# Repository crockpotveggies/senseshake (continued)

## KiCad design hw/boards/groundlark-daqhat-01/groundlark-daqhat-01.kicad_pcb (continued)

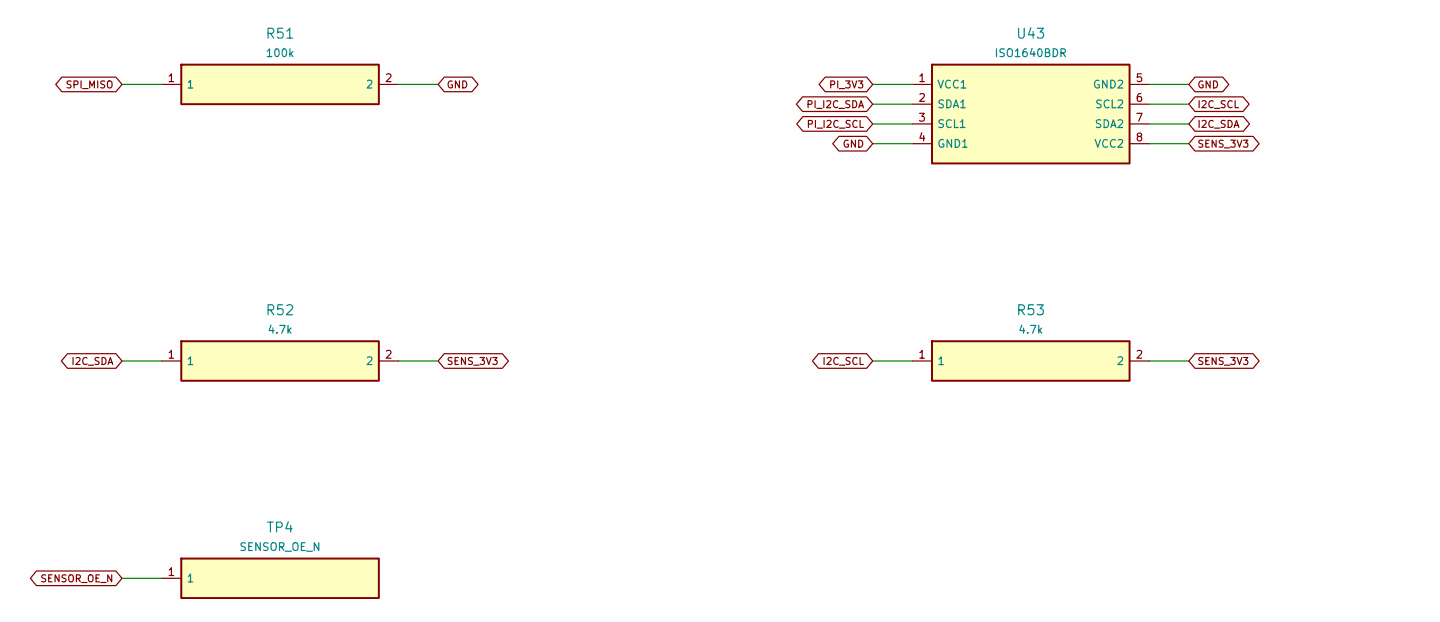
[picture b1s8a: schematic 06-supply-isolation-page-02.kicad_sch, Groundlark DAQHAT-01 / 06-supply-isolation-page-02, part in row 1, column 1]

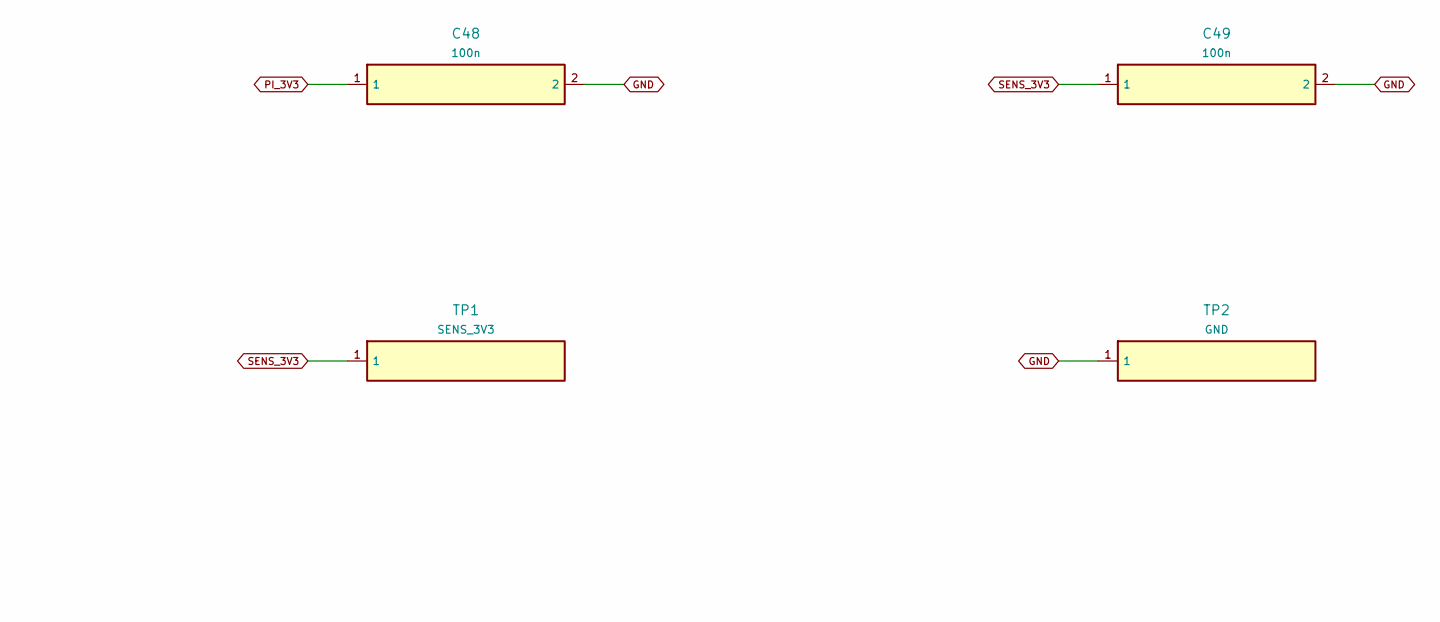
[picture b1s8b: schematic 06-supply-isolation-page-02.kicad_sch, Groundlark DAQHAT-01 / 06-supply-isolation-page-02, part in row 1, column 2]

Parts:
C48, C49: 100n; Capacitor_SMD__C_0603_1608Metric; MPN GRM188R71H104KA93D
R51: 100k; Resistor_SMD__R_0603_1608Metric; MPN RC0603FR-07100KL
R52, R53: 4.7k; Resistor_SMD__R_0603_1608Metric; MPN RC0603FR-074K7L
TP1: SENS_3V3; TestPoint__TestPoint_Pad_D1.5mm; MPN SENS_3V3
TP2: GND; TestPoint__TestPoint_Pad_D1.5mm; MPN GND
TP4: SENSOR_OE_N; TestPoint__TestPoint_Pad_D1.5mm; MPN SENSOR_OE_N
U43: ISO1640BDR; Package_SO__SOIC-8_3.9x4.9mm_P1.27mm; MPN ISO1640BDR

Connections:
GND: C48.2, C49.2, R51.2, TP2.1, U43.4 (GND1), U43.5 (GND2); also elsewhere on the board
I2C_SCL: R53.1, U43.6 (SCL2); also elsewhere on the board
I2C_SDA: R52.1, U43.7 (SDA2); also elsewhere on the board
PI_3V3: C48.1, U43.1 (VCC1); also elsewhere on the board
PI_I2C_SCL: U43.3 (SCL1); also elsewhere on the board
PI_I2C_SDA: U43.2 (SDA1); also elsewhere on the board
SENSOR_OE_N: TP4.1; also elsewhere on the board
SENS_3V3: C49.1, R52.2, R53.2, TP1.1, U43.8 (VCC2); also elsewhere on the board
SPI_MISO: R51.1; also elsewhere on the board

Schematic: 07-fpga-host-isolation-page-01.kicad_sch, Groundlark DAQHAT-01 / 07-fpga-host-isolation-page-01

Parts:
C75, C76, C77: 100n; Capacitor_SMD__C_0603_1608Metric; MPN GRM188R71H104KA93D
Q1: 2N7002; Package_TO_SOT_SMD__SOT-23; MPN 2N7002
R61: 47; Resistor_SMD__R_0603_1608Metric; MPN RC0603FR-0747RL
R62, R66: 100k; Resistor_SMD__R_0603_1608Metric; MPN RC0603FR-07100KL
R63, R64: 10k; Resistor_SMD__R_0603_1608Metric; MPN RC0603FR-0710KL
R65: 1k; Resistor_SMD__R_0603_1608Metric; MPN RC0603FR-071KL
U51: TXU0202DCUR; Package_SO__VSSOP-8_2.3x2mm_P0.5mm; MPN TXU0202DCUR
U52: TLV803EA30DBZR; Package_TO_SOT_SMD__SOT-23; MPN TLV803EA30DBZR

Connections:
FPGA_3V3: C76.1, C77.1, R63.2, R64.2, U51.7 (VCCB), U52.3 (VDD); also elsewhere on the board
FPGA_IO_ENABLE: R62.1, U51.6 (OE); also elsewhere on the board
FPGA_RESET_GATE: Q1.1 (G), R65.2, R66.1
FPGA_RESET_GPIO: R65.1; also elsewhere on the board
FPGA_RESET_N: Q1.3 (D), R64.1, U52.2 (RESET_N); also elsewhere on the board
FPGA_UART_DRIVE: R61.1, U51.8 (B1Y_OUT)
FPGA_UART_RX: R61.2, R63.1; also elsewhere on the board
FPGA_UART_TX: U51.1 (B2_IN); also elsewhere on the board
GND: C75.2, C76.2, C77.2, Q1.2 (S), R62.2, R66.2, U51.2 (GND), U52.1 (GND); also elsewhere on the board
PI_3V3: C75.1, U51.3 (VCCA); also elsewhere on the board
PI_UART_RX: U51.4 (A2Y_OUT); also elsewhere on the board
PI_UART_TX: U51.5 (A1_IN); also elsewhere on the board

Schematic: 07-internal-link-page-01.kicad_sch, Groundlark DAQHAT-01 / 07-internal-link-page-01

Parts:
C100, C101, C102, C103, C104, C105: 100n; Capacitor_SMD__C_0603_1608Metric; MPN GRM188R71H104KA93D
U100, U101: TMUX1574PWR; Package_SO__TSSOP-16_4.4x5mm_P0.65mm; MPN TMUX1574PWR
U102: TCA9534PWR; Package_SO__TSSOP-16_4.4x5mm_P0.65mm; MPN TCA9534PWR
U103: SN74LVC1G10DCKR; Package_TO_SOT_SMD__SOT-363_SC-70-6; MPN SN74LVC1G10DCKR
U104, U105: TLV809EA30DBZR; Package_TO_SOT_SMD__SOT-23; MPN TLV809EA30DBZR

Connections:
FPGA_3V3: C100.1, C101.1, C103.1, C105.1, U100.16 (VDD), U101.16 (VDD), U103.5 (VCC), U105.3 (VDD); also elsewhere on the board
FPGA_LINK_CS_N: U101.2 (S1A); also elsewhere on the board
FPGA_LINK_DQ0: U100.5 (S2A); also elsewhere on the board
FPGA_LINK_DQ1: U100.11 (S3A); also elsewhere on the board
FPGA_LINK_DQ2: U100.14 (S4A); also elsewhere on the board
FPGA_LINK_DQ3: U101.5 (S2A); also elsewhere on the board
FPGA_LINK_SCLK: U100.2 (S1A); also elsewhere on the board
GND: C100.2, C101.2, C102.2, C103.2, C104.2, C105.2, U100.8 (GND), U101.8 (GND), U101.9 (D3), U101.10 (S3B), U101.11 (S3A), U101.12 (D4), U101.13 (S4B), U101.14 (S4A), U102.1 (A0), U102.2 (A1), U102.3 (A2), U102.6 (P2), U102.7 (P3), U102.8 (GND), U102.9 (P4), U102.10 (P5), U102.11 (P6), U102.12 (P7), U103.2 (GND), U104.1 (GND), U105.1 (GND); also elsewhere on the board
JTAG_TCK: U100.3 (S1B); also elsewhere on the board
JTAG_TDI: U100.6 (S2B); also elsewhere on the board
JTAG_TDO: U100.10 (S3B); also elsewhere on the board
JTAG_TMS: U100.13 (S4B); also elsewhere on the board
LINK_ARMED_REQUEST: U103.1 (A); also elsewhere on the board
LINK_CS_N: U101.4 (D1); also elsewhere on the board
LINK_DQ0: U100.7 (D2); also elsewhere on the board
LINK_DQ1: U100.9 (D3); also elsewhere on the board
LINK_DQ2: U100.12 (D4); also elsewhere on the board
LINK_DQ3: U101.7 (D2); also elsewhere on the board
LINK_FPGA_GOOD: U103.6 (C), U105.2 (RESET_N); also elsewhere on the board
LINK_JTAG_SEL: U100.1 (SEL), U101.1 (SEL), U102.4 (P0_MODE); also elsewhere on the board
LINK_OE_N: U100.15 (EN_N), U101.15 (EN_N), U103.4 (Y); also elsewhere on the board
LINK_PI_GOOD: U103.3 (B), U104.2 (RESET_N); also elsewhere on the board
LINK_REQUEST: U102.5 (P1_ENABLE); also elsewhere on the board
LINK_SCLK: U100.4 (D1); also elsewhere on the board
PI_3V3: C102.1, C104.1, U102.16 (VCC), U104.3 (VDD); also elsewhere on the board
PI_I2C_SCL: U102.14 (SCL); also elsewhere on the board
PI_I2C_SDA: U102.15 (SDA); also elsewhere on the board
u101-3: U101.3 (S1B)
u101-6: U101.6 (S2B)
u102-13: U102.13 (INT_N)

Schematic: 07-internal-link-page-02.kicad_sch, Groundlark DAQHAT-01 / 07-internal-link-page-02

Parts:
R100, R101, R102, R103, R104, R105: 22; Resistor_SMD__R_0603_1608Metric; MPN RC0603FR-0722RL
R106, R107, R108, R109, R110, R111: 10k; Resistor_SMD__R_0603_1608Metric; MPN RC0603FR-0710KL

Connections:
FPGA_3V3: R108.2, R111.2; also elsewhere on the board
FPGA_LINK_CS_N: R111.1; also elsewhere on the board
GND: R106.2, R107.2, R109.2, R110.2; also elsewhere on the board
LINK_CS_N: R104.2; also elsewhere on the board
LINK_DQ0: R101.2; also elsewhere on the board
LINK_DQ1: R102.2; also elsewhere on the board
LINK_DQ2: R103.2; also elsewhere on the board
LINK_DQ3: R105.2; also elsewhere on the board
LINK_FPGA_GOOD: R110.1; also elsewhere on the board
LINK_JTAG_SEL: R106.1; also elsewhere on the board
LINK_OE_N: R108.1; also elsewhere on the board
LINK_PI_GOOD: R109.1; also elsewhere on the board
LINK_REQUEST: R107.1; also elsewhere on the board
LINK_SCLK: R100.2; also elsewhere on the board
PI_LINK_CS_N: R104.1; also elsewhere on the board
PI_LINK_DQ0: R101.1; also elsewhere on the board
PI_LINK_DQ1: R102.1; also elsewhere on the board
PI_LINK_DQ2: R103.1; also elsewhere on the board
PI_LINK_DQ3: R105.1; also elsewhere on the board
PI_LINK_SCLK: R100.1; also elsewhere on the board

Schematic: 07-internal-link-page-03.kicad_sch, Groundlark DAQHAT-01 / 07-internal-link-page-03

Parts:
C106: 100n; Capacitor_SMD__C_0603_1608Metric; MPN GRM188R71H104KA93D
R112, R114, R116, R117: 100k; Resistor_SMD__R_0603_1608Metric; MPN RC0603FR-07100KL
R113, R115: 10k; Resistor_SMD__R_0603_1608Metric; MPN RC0603FR-0710KL
U106: SN74LVC1G08DCKR; Package_TO_SOT_SMD__SOT-353_SC-70-5; MPN SN74LVC1G08DCKR

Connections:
FPGA_3V3: C106.1, R113.2, R115.2, U106.5 (VCC); also elsewhere on the board
FPGA_IO_ENABLE: U106.2 (B); also elsewhere on the board
FPGA_LINK_DQ2: R116.1; also elsewhere on the board
FPGA_LINK_DQ3: R117.1; also elsewhere on the board
FPGA_LINK_SCLK: R112.1; also elsewhere on the board
GND: C106.2, R112.2, R114.2, R116.2, R117.2, U106.3 (GND); also elsewhere on the board
JTAG_TCK: R114.1; also elsewhere on the board
JTAG_TDI: R115.1; also elsewhere on the board
JTAG_TMS: R113.1; also elsewhere on the board
LINK_ARMED_REQUEST: U106.4 (Y); also elsewhere on the board
LINK_REQUEST: U106.1 (A); also elsewhere on the board

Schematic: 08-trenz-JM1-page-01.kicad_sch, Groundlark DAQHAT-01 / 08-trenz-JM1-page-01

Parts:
J80: LSHM-150-04.0-L-DV-A-S-K-TR; TZ_TZ100; MPN LSHM-150-04.0-L-DV-A-S-K-TR

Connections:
3: J80.3
5: J80.5
9: J80.9
11: J80.11
15: J80.15
17: J80.17
20: J80.20
21: J80.21
22: J80.22
23: J80.23
24: J80.24
26: J80.26
28: J80.28
32: J80.32
34: J80.34
35: J80.35
36: J80.36
37: J80.37
38: J80.38
39: J80.39
40: J80.40
41: J80.41
42: J80.42
44: J80.44
45: J80.45
46: J80.46
47: J80.47
48: J80.48
49: J80.49
50: J80.50
51: J80.51
52: J80.52
55: J80.55
56: J80.56
57: J80.57
58: J80.58
59: J80.59
60: J80.60
61: J80.61
62: J80.62
65: J80.65
66: J80.66
67: J80.67
68: J80.68
69: J80.69
70: J80.70
71: J80.71
72: J80.72
75: J80.75
76: J80.76
77: J80.77
78: J80.78
79: J80.79
80: J80.80
81: J80.81
82: J80.82
84: J80.84
85: J80.85
86: J80.86
87: J80.87
88: J80.88
91: J80.91
92: J80.92
93: J80.93
94: J80.94
95: J80.95
96: J80.96
97: J80.97
98: J80.98
99: J80.99
100: J80.100
FPGA_3V3: J80.10, J80.12, J80.13; also elsewhere on the board
FPGA_EN1: J80.27; also elsewhere on the board
FPGA_JTAGEN: J80.90; also elsewhere on the board
FPGA_MODE: J80.31
FPGA_NOSEQ: J80.8; also elsewhere on the board
FPGA_PGOOD: J80.29
FPGA_VIN: J80.2, J80.4, J80.6, J80.14, J80.16; also elsewhere on the board
GND: J80.1, J80.7, J80.19, J80.25, J80.30, J80.33, J80.43, J80.53, J80.54, J80.63, J80.64, J80.73, J80.74, J80.83, J80.89, J80.101; also elsewhere on the board
j80-18: J80.18

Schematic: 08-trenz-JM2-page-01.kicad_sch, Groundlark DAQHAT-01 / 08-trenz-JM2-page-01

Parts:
J81: LSHM-150-04.0-L-DV-A-S-K-TR; TZ_TZ100; MPN LSHM-150-04.0-L-DV-A-S-K-TR

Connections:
6: J81.6
16: J81.16
25: J81.25
27: J81.27
29: J81.29
30: J81.30
43: J81.43
53: J81.53
54: J81.54
63: J81.63
64: J81.64
73: J81.73
74: J81.74
83: J81.83
90: J81.90
FPGA_3V3: J81.2, J81.4, J81.8, J81.9, J81.10, J81.11, J81.92; also elsewhere on the board
FPGA_CONFIG_RESET_N: J81.17; also elsewhere on the board
FPGA_LINK_CS_N: J81.23; also elsewhere on the board
FPGA_LINK_DQ0: J81.22; also elsewhere on the board
FPGA_LINK_DQ1: J81.24; also elsewhere on the board
FPGA_LINK_DQ2: J81.26; also elsewhere on the board
FPGA_LINK_DQ3: J81.28; also elsewhere on the board
FPGA_LINK_SCLK: J81.21; also elsewhere on the board
FPGA_RESET_N: J81.13; also elsewhere on the board
FPGA_UART_RX: J81.12; also elsewhere on the board
FPGA_UART_TX: J81.14; also elsewhere on the board
FPGA_VIN: J81.1, J81.3, J81.5, J81.7; also elsewhere on the board
GND: J81.19, J81.39, J81.40, J81.49, J81.50, J81.59, J81.60, J81.69, J81.70, J81.79, J81.80, J81.89, J81.101; also elsewhere on the board
JTAG_TCK: J81.100; also elsewhere on the board
JTAG_TDI: J81.96; also elsewhere on the board
JTAG_TDO: J81.98; also elsewhere on the board
JTAG_TMS: J81.94; also elsewhere on the board
j81-15: J81.15
j81-18: J81.18
j81-20: J81.20
j81-31: J81.31
j81-32: J81.32
j81-33: J81.33
j81-34: J81.34
j81-35: J81.35
j81-36: J81.36
j81-37: J81.37
j81-38: J81.38
j81-41: J81.41
j81-42: J81.42
j81-44: J81.44
j81-45: J81.45
j81-46: J81.46
j81-47: J81.47
j81-48: J81.48
j81-51: J81.51
j81-52: J81.52
j81-55: J81.55
j81-56: J81.56
j81-57: J81.57
j81-58: J81.58
j81-61: J81.61
j81-62: J81.62
j81-65: J81.65
j81-66: J81.66
j81-67: J81.67
j81-68: J81.68
j81-71: J81.71
j81-72: J81.72
j81-75: J81.75
j81-76: J81.76
j81-77: J81.77
j81-78: J81.78
j81-81: J81.81
j81-82: J81.82
j81-84: J81.84
j81-85: J81.85
j81-86: J81.86
j81-87: J81.87
j81-88: J81.88
j81-91: J81.91
j81-93: J81.93
j81-95: J81.95
j81-97: J81.97
j81-99: J81.99

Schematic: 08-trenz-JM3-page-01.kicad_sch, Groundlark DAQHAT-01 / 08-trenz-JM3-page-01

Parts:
J82: LSHM-130-04.0-L-DV-A-S-K-TR; TZ_TZ60; MPN LSHM-130-04.0-L-DV-A-S-K-TR

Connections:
1: J82.1
2: J82.2
4: J82.4
7: J82.7
8: J82.8
10: J82.10
13: J82.13
14: J82.14
19: J82.19
GND: J82.5, J82.6, J82.11, J82.12, J82.17, J82.18, J82.23, J82.24, J82.29, J82.30, J82.35, J82.36, J82.45, J82.46, J82.61; also elsewhere on the board
j82-3: J82.3
j82-9: J82.9
j82-15: J82.15
j82-16: J82.16
j82-20: J82.20
j82-21: J82.21
j82-22: J82.22
j82-25: J82.25
j82-26: J82.26
j82-27: J82.27
j82-28: J82.28
j82-31: J82.31
j82-32: J82.32
j82-33: J82.33
j82-34: J82.34
j82-37: J82.37
j82-38: J82.38
j82-39: J82.39
j82-40: J82.40
j82-41: J82.41
j82-42: J82.42
j82-43: J82.43
j82-44: J82.44
j82-47: J82.47
j82-48: J82.48
j82-49: J82.49
j82-50: J82.50
j82-51: J82.51
j82-52: J82.52
j82-53: J82.53
j82-54: J82.54
j82-55: J82.55
j82-56: J82.56
j82-57: J82.57
j82-58: J82.58
j82-59: J82.59
j82-60: J82.60

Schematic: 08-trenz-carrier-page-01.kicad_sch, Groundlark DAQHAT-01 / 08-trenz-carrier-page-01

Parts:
F80: 0467005.NR; TZ_TZ_FUSE; MPN 0467005.NR
J83: 1715721; TZ_TZ_POWER; MPN 1715721
JP80, JP81: TSW-102-07-G-S; TZ_TZ_JP; MPN TSW-102-07-G-S
R80, R81: 10k; Resistor_SMD__R_0603_1608Metric; MPN RC0603FR-0710KL

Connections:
EXT_3V3: F80.1, J83.1
FPGA_CONFIG_RESET_N: JP81.1; also elsewhere on the board
FPGA_EN1: JP80.1; also elsewhere on the board
FPGA_JTAGEN: R80.1; also elsewhere on the board
FPGA_NOSEQ: R81.1; also elsewhere on the board
FPGA_VIN: F80.2; also elsewhere on the board
GND: J83.2, JP80.2, JP81.2, R80.2, R81.2; also elsewhere on the board

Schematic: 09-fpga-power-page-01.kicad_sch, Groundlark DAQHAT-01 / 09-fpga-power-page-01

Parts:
C80, C81, C82: 22u; Capacitor_SMD__C_1206_3216Metric; MPN GRM31CR61A226KE19L
C83: 100n; Capacitor_SMD__C_0603_1608Metric; MPN GRM188R71H104KA93D
C84, C85: 4.7u; Capacitor_SMD__C_0805_2012Metric; MPN GRM21BR71A475KA73L

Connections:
FPGA_3V3: C84.1, C85.1; also elsewhere on the board
FPGA_VIN: C80.1, C81.1, C82.1, C83.1; also elsewhere on the board
GND: C80.2, C81.2, C82.2, C83.2, C84.2, C85.2; also elsewhere on the board

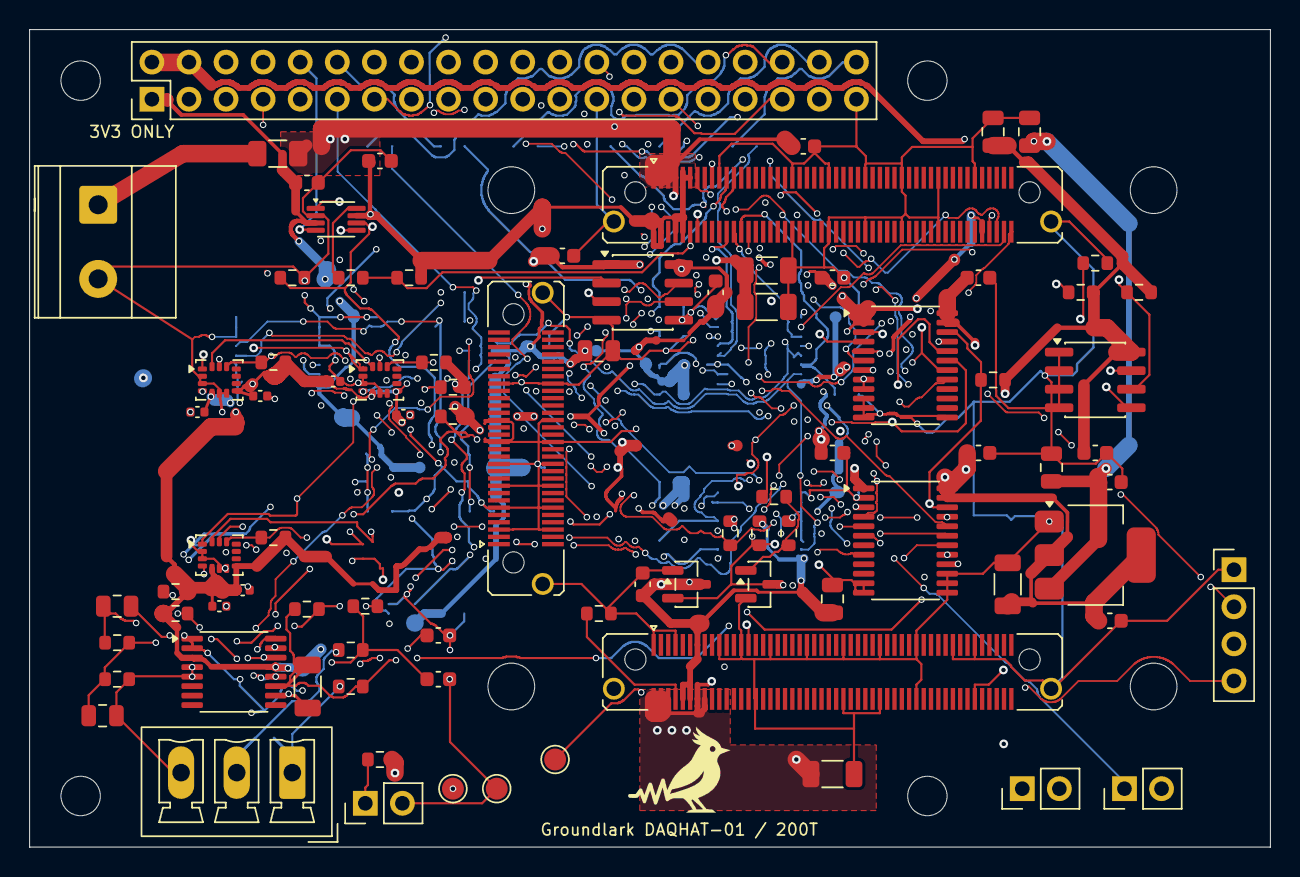
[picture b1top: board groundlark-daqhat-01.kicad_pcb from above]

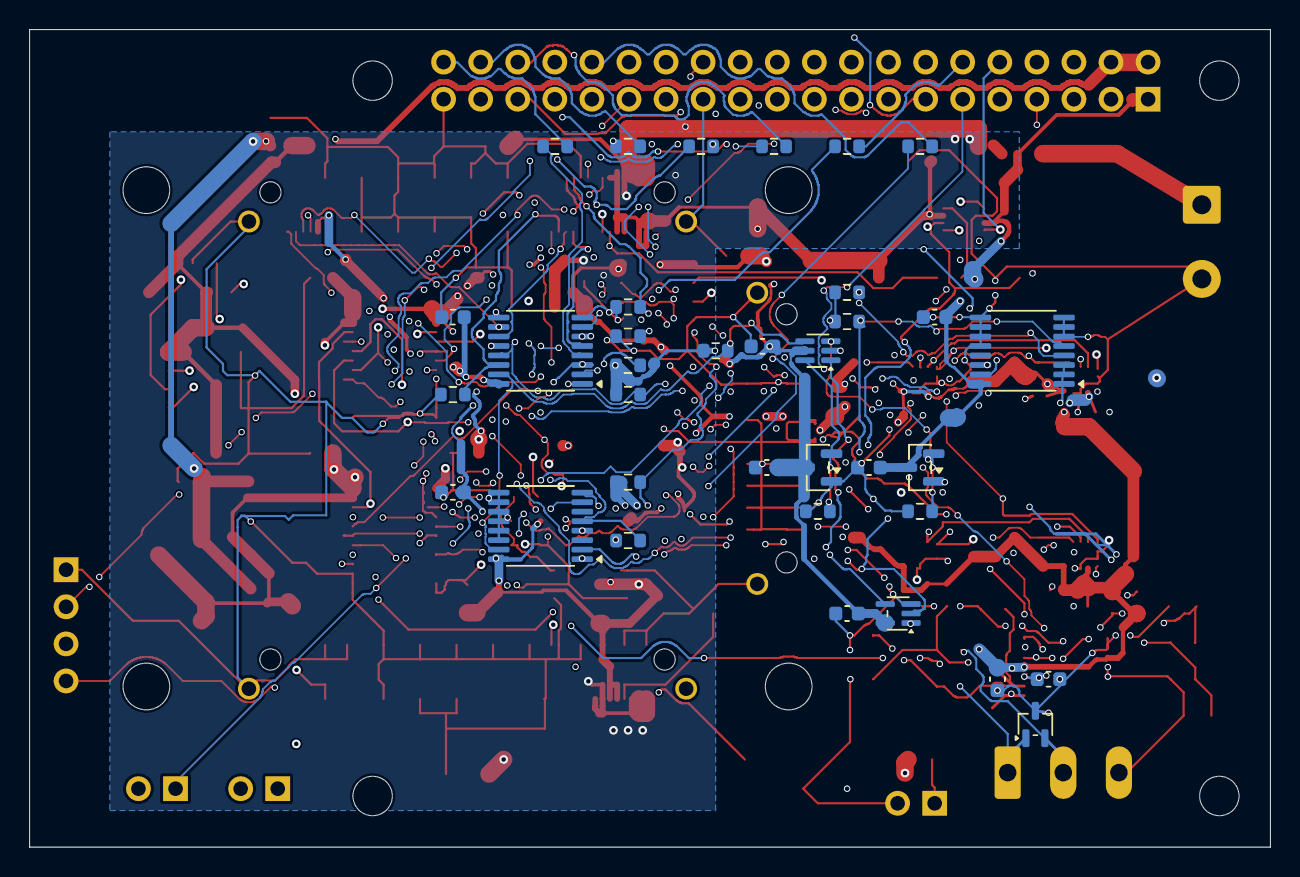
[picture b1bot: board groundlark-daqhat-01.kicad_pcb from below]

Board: 6 copper layers, 85.0 x 56.0 mm, 128 parts (35 on the bottom side), 82 nets.

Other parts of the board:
H1, H2, H3, H4: M2.5 NPTH; MountingHole__MountingHole_2.7mm_M2.5
H80, H81, H82, H83: M3 / 8 mm spacer; TZ_TZ_HOLE

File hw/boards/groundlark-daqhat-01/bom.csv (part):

Reference,Value,MPN,Footprint,DNP,Note
J1,Raspberry Pi 40-pin,Samtec ESQ-120-23-G-D,Connector_PinHeader_2.54mm__PinHeader_2x20_P2.54mm_Vertical,False,"Header land pattern matches bottom mounted socket top-view numbering; tall stack, check Pi 4/5 cooler clearance."
U1,24LC32A,24LC32A-I/SN,Package_SO__SOIC-8_3.9x4.9mm_P1.27mm,False,
R1,3.9k,RC0603FR-073K9L,Resistor_SMD__R_0603_1608Metric,False,
R2,3.9k,RC0603FR-073K9L,Resistor_SMD__R_0603_1608Metric,False,
R3,1k,RC0603FR-071KL,Resistor_SMD__R_0603_1608Metric,False,
JP1,EEPROM write enable,EEPROM write enable,Connector_PinHeader_2.54mm__PinHeader_1x02_P2.54mm_Vertical,False,Fit shunt only while programming ID EEPROM.
C1,100n,GRM188R71H104KA93D,Capacitor_SMD__C_0603_1608Metric,False,
C2,10u,GRM21BR61A106KE19L,Capacitor_SMD__C_0805_2012Metric,False,
C3,10u,GRM21BR61A106KE19L,Capacitor_SMD__C_0805_2012Metric,False,
U11,LSM6DSOTR,LSM6DSOTR,Package_LGA__LGA-14_3x2.5mm_P0.5mm_LayoutBorder3x4y,False,
C12,100n,GRM155R71C104KA88D,Capacitor_SMD__C_0402_1005Metric,False,
C13,100n,GRM155R71C104KA88D,Capacitor_SMD__C_0402_1005Metric,False,
R11,10k,RC0603FR-0710KL,Resistor_SMD__R_0603_1608Metric,False,
U12,LSM6DSOTR,LSM6DSOTR,Package_LGA__LGA-14_3x2.5mm_P0.5mm_LayoutBorder3x4y,False,
C14,100n,GRM155R71C104KA88D,Capacitor_SMD__C_0402_1005Metric,False,
C15,100n,GRM155R71C104KA88D,Capacitor_SMD__C_0402_1005Metric,False,
R12,10k,RC0603FR-0710KL,Resistor_SMD__R_0603_1608Metric,False,
U13,LSM6DSOTR,LSM6DSOTR,Package_LGA__LGA-14_3x2.5mm_P0.5mm_LayoutBorder3x4y,False,
C16,100n,GRM155R71C104KA88D,Capacitor_SMD__C_0402_1005Metric,False,
C17,100n,GRM155R71C104KA88D,Capacitor_SMD__C_0402_1005Metric,False,
R13,10k,RC0603FR-0710KL,Resistor_SMD__R_0603_1608Metric,False,
J4,FPGA test UART/reset,Coldfoot UART service ONLY,Connector_PinHeader_2.54mm__PinHeader_1x04_P2.54mm_Vertical,False,Test points for assembled module UART and active-low reset; do not connect a second driving host.
H1,M2.5 NPTH,M2.5 NPTH,MountingHole__MountingHole_2.7mm_M2.5,False,Nonmagnetic standoffs.
H2,M2.5 NPTH,M2.5 NPTH,MountingHole__MountingHole_2.7mm_M2.5,False,Nonmagnetic standoffs.
H3,M2.5 NPTH,M2.5 NPTH,MountingHole__MountingHole_2.7mm_M2.5,False,Nonmagnetic standoffs.
H4,M2.5 NPTH,M2.5 NPTH,MountingHole__MountingHole_2.7mm_M2.5,False,Nonmagnetic standoffs.
U40,TLV1117LV33DCYR,TLV1117LV33DCYR,Package_TO_SOT_SMD__SOT-223-3_TabPin2,False,
C40,10u,GRM21BR61A106KE19L,Capacitor_SMD__C_0805_2012Metric,False,
C41,100n,GRM188R71H104KA93D,Capacitor_SMD__C_0603_1608Metric,False,
C42,22u,GRM31CR61A226KE19L,Capacitor_SMD__C_1206_3216Metric,False,
C43,100n,GRM188R71H104KA93D,Capacitor_SMD__C_0603_1608Metric,False,
U41,SN74LVC8T245PWR,SN74LVC8T245PWR,Package_SO__TSSOP-24_4.4x7.8mm_P0.65mm,False,
U42,SN74LVC8T245PWR,SN74LVC8T245PWR,Package_SO__TSSOP-24_4.4x7.8mm_P0.65mm,False,
C44,100n,GRM188R71H104KA93D,Capacitor_SMD__C_0603_1608Metric,False,
C45,100n,GRM188R71H104KA93D,Capacitor_SMD__C_0603_1608Metric,False,
C46,100n,GRM188R71H104KA93D,Capacitor_SMD__C_0603_1608Metric,False,
C47,100n,GRM188R71H104KA93D,Capacitor_SMD__C_0603_1608Metric,False,
R50,10k,RC0603FR-0710KL,Resistor_SMD__R_0603_1608Metric,False,
R51,100k,RC0603FR-07100KL,Resistor_SMD__R_0603_1608Metric,False,
U43,ISO1640BDR,ISO1640BDR,Package_SO__SOIC-8_3.9x4.9mm_P1.27mm,False,Power-domain isolation only: grounds are joined. Side-1 VOL max 0.71V requires host VIL >=0.8V; verify Pi revision.
C48,100n,GRM188R71H104KA93D,Capacitor_SMD__C_0603_1608Metric,False,
C49,100n,GRM188R71H104KA93D,Capacitor_SMD__C_0603_1608Metric,False,
R52,4.7k,RC0603FR-074K7L,Resistor_SMD__R_0603_1608Metric,False,
R53,4.7k,RC0603FR-074K7L,Resistor_SMD__R_0603_1608Metric,False,
TP1,SENS_3V3,SENS_3V3,TestPoint__TestPoint_Pad_D1.5mm,False,
TP2,GND,GND,TestPoint__TestPoint_Pad_D1.5mm,False,
TP4,SENSOR_OE_N,SENSOR_OE_N,TestPoint__TestPoint_Pad_D1.5mm,False,
U51,TXU0202DCUR,TXU0202DCUR,Package_SO__VSSOP-8_2.3x2mm_P0.5mm,False,
C75,100n,GRM188R71H104KA93D,Capacitor_SMD__C_0603_1608Metric,False,
C76,100n,GRM188R71H104KA93D,Capacitor_SMD__C_0603_1608Metric,False,
R61,47,RC0603FR-0747RL,Resistor_SMD__R_0603_1608Metric,False,
R62,100k,RC0603FR-07100KL,Resistor_SMD__R_0603_1608Metric,False,
R63,10k,RC0603FR-0710KL,Resistor_SMD__R_0603_1608Metric,False,
U52,TLV803EA30DBZR,TLV803EA30DBZR,Package_TO_SOT_SMD__SOT-23,False,"3.0V falling threshold, 200ms nominal release delay; open-drain output."
C77,100n,GRM188R71H104KA93D,Capacitor_SMD__C_0603_1608Metric,False,
R64,10k,RC0603FR-0710KL,Resistor_SMD__R_0603_1608Metric,False,
Q1,2N7002,2N7002,Package_TO_SOT_SMD__SOT-23,False,Pi GPIO17 HIGH asserts chip reset; does not drive a live voltage into unpowered chip.
R65,1k,RC0603FR-071KL,Resistor_SMD__R_0603_1608Metric,False,
R66,100k,RC0603FR-07100KL,Resistor_SMD__R_0603_1608Metric,False,
J80,LSHM-150-04.0-L-DV-A-S-K-TR,LSHM-150-04.0-L-DV-A-S-K-TR,TZ_TZ100,False,Mates JM1; opposite parity; 8 mm board surface gap
J81,LSHM-150-04.0-L-DV-A-S-K-TR,LSHM-150-04.0-L-DV-A-S-K-TR,TZ_TZ100,False,Mates JM2; opposite parity; 8 mm board surface gap
J82,LSHM-130-04.0-L-DV-A-S-K-TR,LSHM-130-04.0-L-DV-A-S-K-TR,TZ_TZ60,False,Mates JM3; opposite parity; 8 mm board surface gap
J83,1715721,1715721,TZ_TZ_POWER,False,REGULATED 3.3 V ONLY; external current-limited supply; 3 A initial operating budget Shifted left to keep power-terminal tails out of the J86 ribbon corridor.
F80,0467005.NR,0467005.NR,TZ_TZ_FUSE,False,5 A fast fuse; not reverse-polarity or overvoltage protection
JP80,TSW-102-07-G-S,TSW-102-07-G-S,TZ_TZ_JP,False,Fit shunt to DISABLE module; open enables on-board sequence
JP81,TSW-102-07-G-S,TSW-102-07-G-S,TZ_TZ_JP,False,Fit shunt to request module configuration reset
R80,10k,RC0603FR-0710KL,Resistor_SMD__R_0603_1608Metric,False,FPGA JTAG selection / spare CPLD control idle pull-down
R81,10k,RC0603FR-0710KL,Resistor_SMD__R_0603_1608Metric,False,FPGA JTAG selection / spare CPLD control idle pull-down
C80,22u,GRM31CR61A226KE19L,Capacitor_SMD__C_1206_3216Metric,False,Carrier local decoupling; module contains core decoupling
C81,22u,GRM31CR61A226KE19L,Capacitor_SMD__C_1206_3216Metric,False,Carrier local decoupling; module contains core decoupling
C82,22u,GRM31CR61A226KE19L,Capacitor_SMD__C_1206_3216Metric,False,Carrier local decoupling; module contains core decoupling
C83,100n,GRM188R71H104KA93D,Capacitor_SMD__C_0603_1608Metric,False,Carrier local decoupling; module contains core decoupling
C84,4.7u,GRM21BR71A475KA73L,Capacitor_SMD__C_0805_2012Metric,False,Carrier local decoupling; module contains core decoupling
C85,4.7u,GRM21BR71A475KA73L,Capacitor_SMD__C_0805_2012Metric,False,Carrier local decoupling; module contains core decoupling
H80,M3 / 8 mm spacer,M3 / 8 mm spacer,TZ_TZ_HOLE,False,
H81,M3 / 8 mm spacer,M3 / 8 mm spacer,TZ_TZ_HOLE,False,
H82,M3 / 8 mm spacer,M3 / 8 mm spacer,TZ_TZ_HOLE,False,
H83,M3 / 8 mm spacer,M3 / 8 mm spacer,TZ_TZ_HOLE,False,
U22,ADS122C04,ADS122C04IPWR,Package_SO__TSSOP-16_4.4x5mm_P0.65mm,False,"I2C 0x40; internal 2.048V reference, gain 64, normal 330 SPS; unused analog/reference inputs open per TI."
J90,GEO + / - / SHIELD,1803439,"Connector_Phoenix_MC__PhoenixContact_MCV_1,5_3-G-3.81_1x03_P3.81mm_Vertical",False,"External passive sensor: 1 positive, 2 negative, 3 cable shield. Mate MC 1,5/3-ST-3,81. Never connect power."
D90,TPD2E2U06,TPD2E2U06DCKR,Package_TO_SOT_SMD__SOT-323_SC-70,False,Connector ESD suppression only; not lightning protection.
R90,1k,RC0603FR-071KL,Resistor_SMD__R_0603_1608Metric,False,Matched series input filter / current limiting.
R91,1k,RC0603FR-071KL,Resistor_SMD__R_0603_1608Metric,False,
C90,100n C0G,C3216C0G1H104J160AA,Capacitor_SMD__C_1206_3216Metric,False,C0G differential filter; no piezoelectric X7R on signal path.
C91,1n C0G,C0603C102J5GACTU,Capacitor_SMD__C_0603_1608Metric,False,
C92,1n C0G,C0603C102J5GACTU,Capacitor_SMD__C_0603_1608Metric,False,
R92,1M,RC0603FR-071ML,Resistor_SMD__R_0603_1608Metric,False,
R93,1M,RC0603FR-071ML,Resistor_SMD__R_0603_1608Metric,False,
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
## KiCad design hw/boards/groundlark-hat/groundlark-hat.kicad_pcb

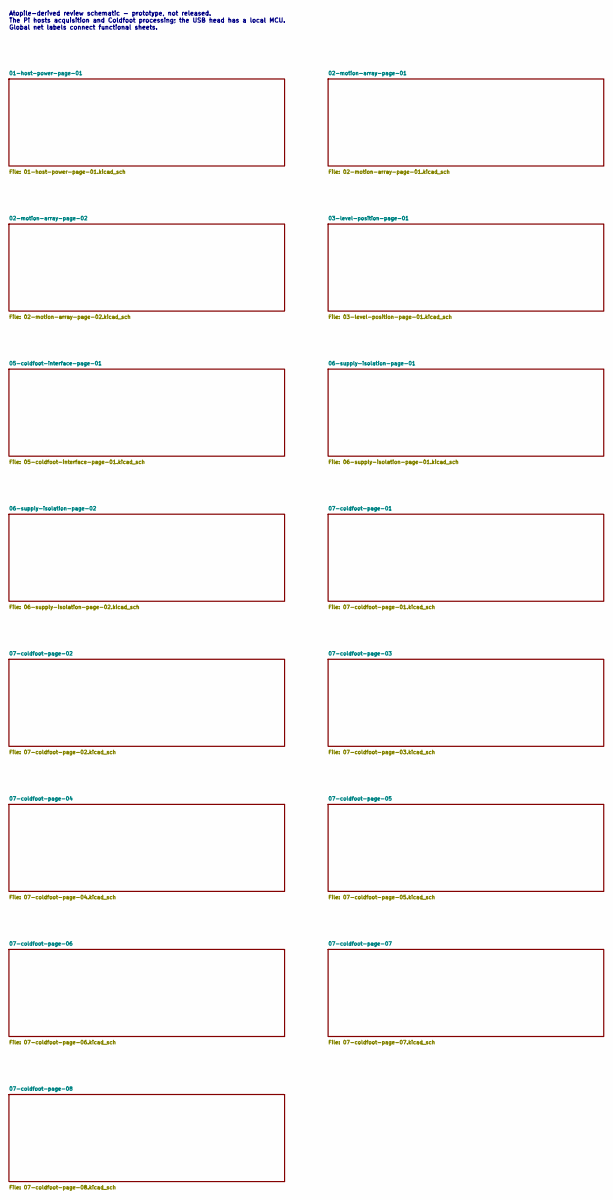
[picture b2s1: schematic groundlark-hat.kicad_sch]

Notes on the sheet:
Atopile-derived review schematic - prototype, not released. The Pi hosts acquisition and Coldfoot processing; the USB head has a local MCU. Global net labels connect functional sheets.
